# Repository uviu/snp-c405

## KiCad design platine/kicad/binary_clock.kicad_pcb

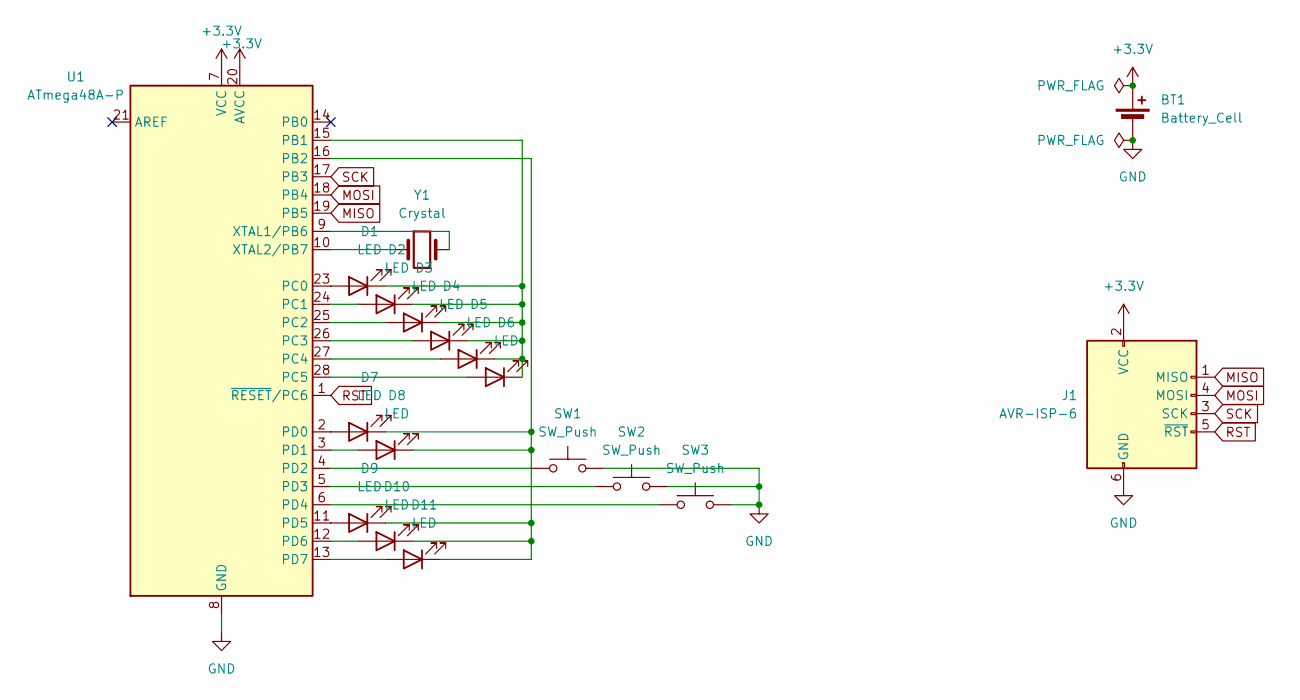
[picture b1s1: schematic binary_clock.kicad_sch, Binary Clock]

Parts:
BT1: Battery_Cell; BatteryHolder_Keystone_103_1x20mm
D1, D2, D3, D4, D5, D6, D7, D8, D9, D10, D11: LED; LED_D3.0mm
J1: AVR-ISP-6; PinSocket_2x03_P2.54mm_Vertical
SW1, SW2, SW3: SW_Push; SW_PUSH_6mm
U1: ATmega48A-P; DIP-28_W7.62mm
Y1: Crystal; Crystal_DS10_D1.0mm_L4.3mm_Vertical

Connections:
+3.3V: BT1.1 (+), J1.2 (VCC), U1.7 (VCC), U1.20 (AVCC)
GND: BT1.2 (-), J1.6 (GND), SW1.2, SW2.2, SW3.2, U1.8 (GND), U1.22 (GND)
MISO: J1.1 (MISO), U1.19 (PB5)
MOSI: J1.4 (MOSI), U1.18 (PB4)
unnamed: D1.2 (A), U1.23 (PC0)
unnamed: D1.1 (K), D2.1 (K), D3.1 (K), D4.1 (K), D5.1 (K), D6.1 (K), U1.15 (PB1)
unnamed: D2.2 (A), U1.24 (PC1)
unnamed: D3.2 (A), U1.25 (PC2)
unnamed: D4.2 (A), U1.26 (PC3)
unnamed: D5.2 (A), U1.27 (PC4)
unnamed: D6.2 (A), U1.28 (PC5)
unnamed: D7.2 (A), U1.2 (PD0)
unnamed: D8.2 (A), U1.3 (PD1)
unnamed: D9.2 (A), U1.11 (PD5)
unnamed: D10.2 (A), U1.12 (PD6)
unnamed: D7.1 (K), D8.1 (K), D9.1 (K), D10.1 (K), D11.1 (K), U1.16 (PB2)
unnamed: D11.2 (A), U1.13 (PD7)
unnamed: SW1.1, U1.4 (PD2)
unnamed: SW2.1, U1.5 (PD3)
unnamed: SW3.1, U1.6 (PD4)
unnamed: U1.9 (XTAL1/PB6), Y1.2
unnamed: U1.10 (XTAL2/PB7), Y1.1
RST: J1.5 (~RST), U1.1 (~RESET/PC6)
SCK: J1.3 (SCK), U1.17 (PB3)

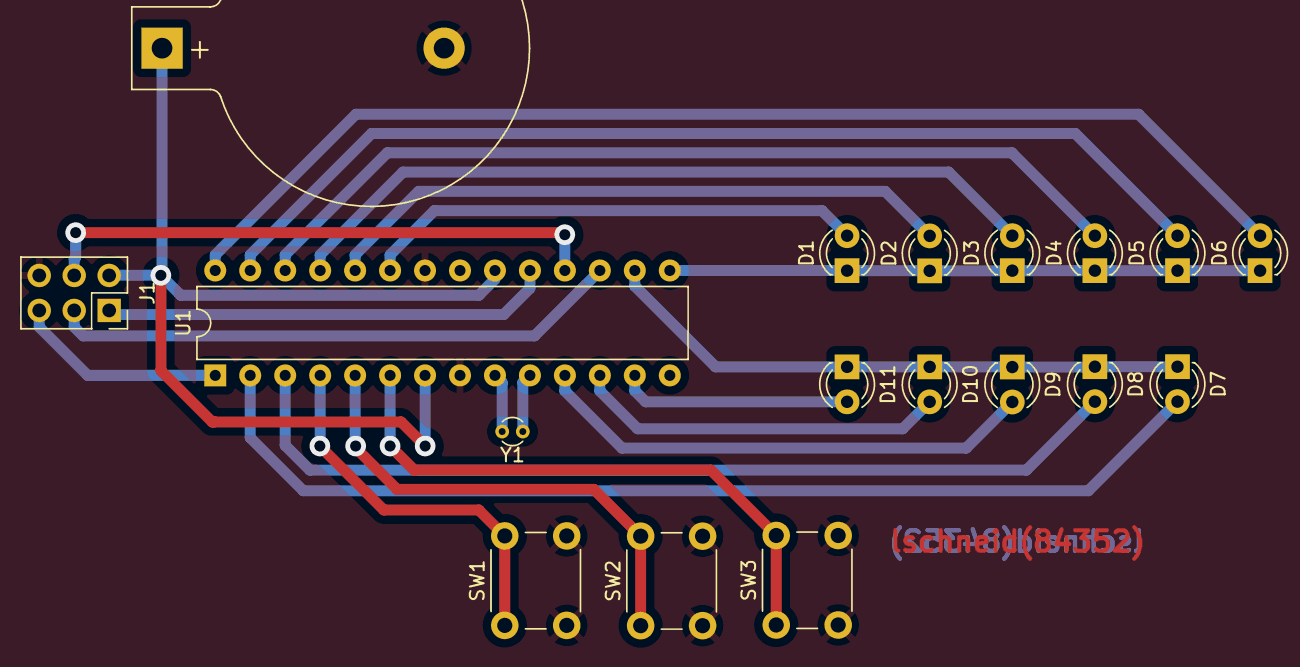
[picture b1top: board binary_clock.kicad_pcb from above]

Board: 2 copper layers, 18 parts (0 on the bottom side), 24 nets.

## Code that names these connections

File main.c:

/*
  Revised Binary Clock Code with Deep Sleep Mode on Brightness Button
  Buttons:
    - PD2 (INT0): Minutes button
    - PD3 (INT1): Hours button
    - PD4: Brightness button (now with deep sleep)
  Cathodes:
    - PB1: Minutes (PWM)
    - PB2: Hours (PWM)
  Displays:
    - Hours: PD0, PD1, PD5, PD6, PD7
    - Minutes: PC0-PC5
  Crystal: PB6/PB7
*/

#include <avr/io.h>
#include <avr/interrupt.h>
#include <util/delay.h>
#include <avr/sleep.h>

volatile uint8_t seconds = 50;
volatile uint8_t minutes = 30;
volatile uint8_t hours = 12;
volatile uint8_t brightness_stage = 0;
volatile uint8_t enter_sleep_flag = 0; // Flag to trigger sleep mode

const uint8_t brightness_levels[] = {254, 248, 156, 0}; // Brightness levels (4 stages)

// Timer2 for timekeeping (1 Hz interrupt)
void setup_timer2() {
    ASSR |= (1 << AS2); // Asynchronous mode (external crystal)
    TCCR2A = 0; // Normal mode
    TCCR2B = (1 << CS22) | (1 << CS20); // Prescaler 128
    TIMSK2 = (1 << TOIE2); // Enable overflow interrupt
    while (ASSR & ((1 << TCR2BUB) | (1 << TCR2AUB) | (1 << OCR2AUB) | (1 << TCN2UB)));
}

// Timer1 for PWM on PB1 and PB2
void setup_timer1() {
    TCCR1A = (1 << WGM10) | (1 << COM1A1) | (1 << COM1B1); // Fast PWM, non-inverting
    TCCR1B = (1 << WGM12) | (1 << CS11); // Prescaler 8
    OCR1A = brightness_levels[brightness_stage]; // Initial brightness
    OCR1B = brightness_levels[brightness_stage];
}

void setup_ports() {
    DDRC |= 0x3F; // PC0-PC5 as outputs (minutes)
    DDRD |= (1 << PD0) | (1 << PD1) | (1 << PD5) | (1 << PD6) | (1 << PD7); // Hours
    DDRD &= ~((1 << PD2) | (1 << PD3) | (1 << PD4)); // Buttons as inputs
    PORTD |= (1 << PD2) | (1 << PD3) | (1 << PD4); // Enable pull-ups
    DDRB |= (1 << PB1) | (1 << PB2); // PWM outputs
}

void setup_external_interrupts() {
    EICRA |= (1 << ISC01) | (1 << ISC11); // INT0/1 on falling edge
    EIMSK |= (1 << INT0) | (1 << INT1); // Enable interrupts
}

// Update displays with current time
void update_display() {
    PORTC = (PORTC & ~0x3F) | (minutes & 0x3F); // Minutes

    uint8_t hr = hours & 0x1F;
    uint8_t hour_output = ((hr & 0x01) << 7) | ((hr & 0x02) << 5) | ((hr & 0x04) << 3) |
                         ((hr & 0x08) >> 2) | ((hr & 0x10) >> 4);
    PORTD = (PORTD & ~0xE3) | hour_output; // Mask PD0, PD1, PD5-PD7
}

// Timer2 overflow ISR (1 Hz)
ISR(TIMER2_OVF_vect) {
    //switch when messuring via counter
    seconds++;
    //minutes++;
    if (seconds >= 60) {
        seconds = 0;
        minutes++;
        if (minutes >= 60) {
            minutes = 0;
            hours++;
            if (hours >= 24) hours = 0;
        }
    }

    // Poll brightness button (PD4)
    if (!(PIND & (1 << PD4))) {
        _delay_ms(5);
        if (!(PIND & (1 << PD4))) {
            brightness_stage = (brightness_stage + 1) % 4; // Cycle 0-3

            // If cycled to 0 (after 3), trigger sleep
            if (brightness_stage == 0) enter_sleep_flag = 1;

            OCR1A = brightness_levels[brightness_stage];
            OCR1B = brightness_levels[brightness_stage];
            while (!(PIND & (1 << PD4))); // Wait for release
            _delay_ms(5);
        }
    }
    if (!enter_sleep_flag) update_display();
}

// INT0 (minutes) and INT1 (hours) handlers
ISR(INT0_vect) {
    _delay_ms(5);
    if (!(PIND & (1 << PD2))) {
        minutes++;
        seconds = 0;
        if (minutes >= 60) {
            minutes = 0;
            hours++;
            if (hours >= 24)
                hours = 0;
        }
        update_display();
    }
}

ISR(INT1_vect) {
    _delay_ms(5);
    if (!(PIND & (1 << PD3))) {
        hours++;
        if (hours >= 24) hours = 0;
        update_display();
    }
}

// Pin change ISR for PD4 (wake from sleep)
ISR(PCINT2_vect) {
    // No action needed; just wakes the MCU
    enter_sleep_flag = 0;
}

int main(void) {
    setup_ports();
    setup_timer2();
    setup_timer1();
    setup_external_interrupts();

    // Initially disable PCINT for PD4
    PCICR &= ~(1 << PCIE2);
    PCMSK2 &= ~(1 << PCINT20);

    sei();

    while (1) {
        if (enter_sleep_flag) {

            // Turn off displays
            OCR1A = 255;
            OCR1B = 255;

            // Enable PD4 pin change interrupt
            PCICR |= (1 << PCIE2);
            PCMSK2 |= (1 << PCINT20);

            // Enter deep sleep
            set_sleep_mode(SLEEP_MODE_PWR_SAVE);
            sleep_mode();

            // Disable PD4 interrupt
            PCICR &= ~(1 << PCIE2);
            PCMSK2 &= ~(1 << PCINT20);

            // Restore brightness
            brightness_stage = 0;
            OCR1A = brightness_levels[brightness_stage];
            OCR1B = brightness_levels[brightness_stage];
        }else{
            // Enter idle sleep between interrupts
            set_sleep_mode(SLEEP_MODE_IDLE);
            sleep_mode();
        }
    }
    return 0;
}

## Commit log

2025-03-22 Rename main.c to src/main.c
2025-03-22 Rename mainRE.c to src/mainRE.c
2025-03-22 Rename template.c to src/template.c
2025-03-22 Rename schaltplan.png to platine/schematic.png
